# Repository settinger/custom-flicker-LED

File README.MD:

# A different interpretation of "programmable LED"

TL;DR I'm investigating if I can attach a very very small circuit to a through-hole LED to run a custom programmed pattern, similar to a candle-flicker LED.

## The Concept

A flicker LED is an LED that flickers. More specifically, it is a _drop-in replacement_ for a conventional LED—no need to change the current-limiting resistor, no new calculations for forward voltages, it works just the same as a conventional LED. And they're cheap, too! If you want an LED that flickers like a candle (or one that blinks at a set frequency and duty cycle) you are set for life.

But what if you want a different LED light pattern? In my specific case, I want an LED that turns on like a struggling fluorescent bulb. Or one that stays off most of the time, then suddenly lights up the room like lightning. Or a pseudo-status LED that blinks at random frequencies to trick the viewer into thinking some complex process is running. Or...anything, really. A programmable LED!

Do programmable LEDs like this exist? Obviously the WS2812b and similar LEDs exist, and those are frequently called "programmable LEDs". But those are pretty different than, say, a flicker LED. You still need a controller of some variety to tell the WS2812b what pattern to perform, which is not the case for a flicker LED, and not the case for the LEDs I'm envisioning.

## The Circuit

So can it be done? Without designing a custom IC and embedding it in a custom LED casing? I need a solution compatible with a stock LED. And that means the solution needs to exist _in parallel with the LED_. I'm envisioning a small PCB nestled underneath a 5mm through-hole LED. Soldered in place between the existing legs, no cuts or modifications to the LED itself.

What microcontroller is small enough to fit under a 5mm through-hole LED? I know of two: the WLCSP-12 ATtiny20 (1.55×1.43 mm) and the WLP-16 MAX32660 (1.55×1.57 mm). It's true that I've been meaning to get better with ARM systems, but for now I'll stick with the more familiar AVR-based ATtiny20.

Both those microcontrollers require at least 1.8V to operate. A white LED drawing between 1 and 20 mA will have a forward voltage in roughly the 2.4 - 3.1 V range. That means a microcontroller in parallel can be powered while the LED is on! However, if the LED shuts off, the voltage across it drops to 0V and the microcontroller will shut off as well. To get around this, we can make the LED super dim instead of completely turned off. If we use a shunt to get the LED forward voltage into the 1.8 - 2.0 V range, the microcontroller can stay on while the LED light output is undetectable. A TLVH431 adjustable shunt lets us keep the same forward voltage, regardless of if the shunt is carrying 1 mA or 20 mA, which makes things more consistent than a Zener diode can do.

My original plan was to shunt current around the LED using a BJT driven by an I/O pin on the microcontroller. This would be paired with a Zener diode to keep the LED voltage at at least 1.8V, to ensure the microcontroller has enough power. There were some issues with this approach! For one thing, I learned that low-value Zeners have much more variation in their breakdown voltages. A diode sold as a 1.8V Zener might, at a current of 10 mA, have a breakdown voltage closer to 2.6V; this wouldn't dim the LED at all!

Another issue was the transistor. I didn't realize that I could sink ~20 mA directly into these microcontrollers' GPIO pins! In fact, the ATtiny20 GPIO can source/sink 40 mA, and the MAX32660 can do 25. This means the current being diverted around the LED can go through the microcontroller, instead of an external transistor. Thank you to [cpldcpu](https://cpldcpu.wordpress.com) for pointing this out to me! I don't know what led me to think that a BGA ATtiny could handle less current than SOIC or DIP equivalents. That set off a cascade of design adjustments that led to the current very-low-component-count design.

## Putting it together

It's working! [Here is a video of the flicker in action](https://twitter.com/DHammarskjold/status/1491195660074627072). The flicker animation is a port of one kindly provided by [Emily Velasco](https://twitter.com/MLE_Online), which you can obtain in the `code/` folder.

[As you can see here](https://twitter.com/DHammarskjold/status/1490858013917208579), there was a (relatively) large PCB still attached to the LED. Those are the programming pads, so I can tweak the program on the ATtiny20 until I decide to trim off the excess parts.

There are components on both sides of the PCB. I put the ATtiny20 and TLVH431 on first, using a hot plate. Then I programmed the tiny20, and finally I hand-soldered the 0402 passives. I used a 47kΩ and a 68kΩ resistor instead of the desired 4.7kΩ and 7.5kΩ ones because that's what I had on hand.

[Here is a tweet showing my protoboard circuit](https://twitter.com/DHammarskjold/status/1483334537580998658), working as expected with larger versions of each part. This helped me dial in the right resistor values and measure the range of current that kept the board functioning. According to my cheap ammeter, the microcontroller functions properly on a supply as low as 0.5 mA and as high as 20 mA, which I'm thrilled to see.

Please let me know if you have some suggestions for improvements to the fluorescent-flicker animation, or if there are other programmable LED animations you'd like to see! I have a few ideas for a 5mm RGB LED, but that's a project for another time....

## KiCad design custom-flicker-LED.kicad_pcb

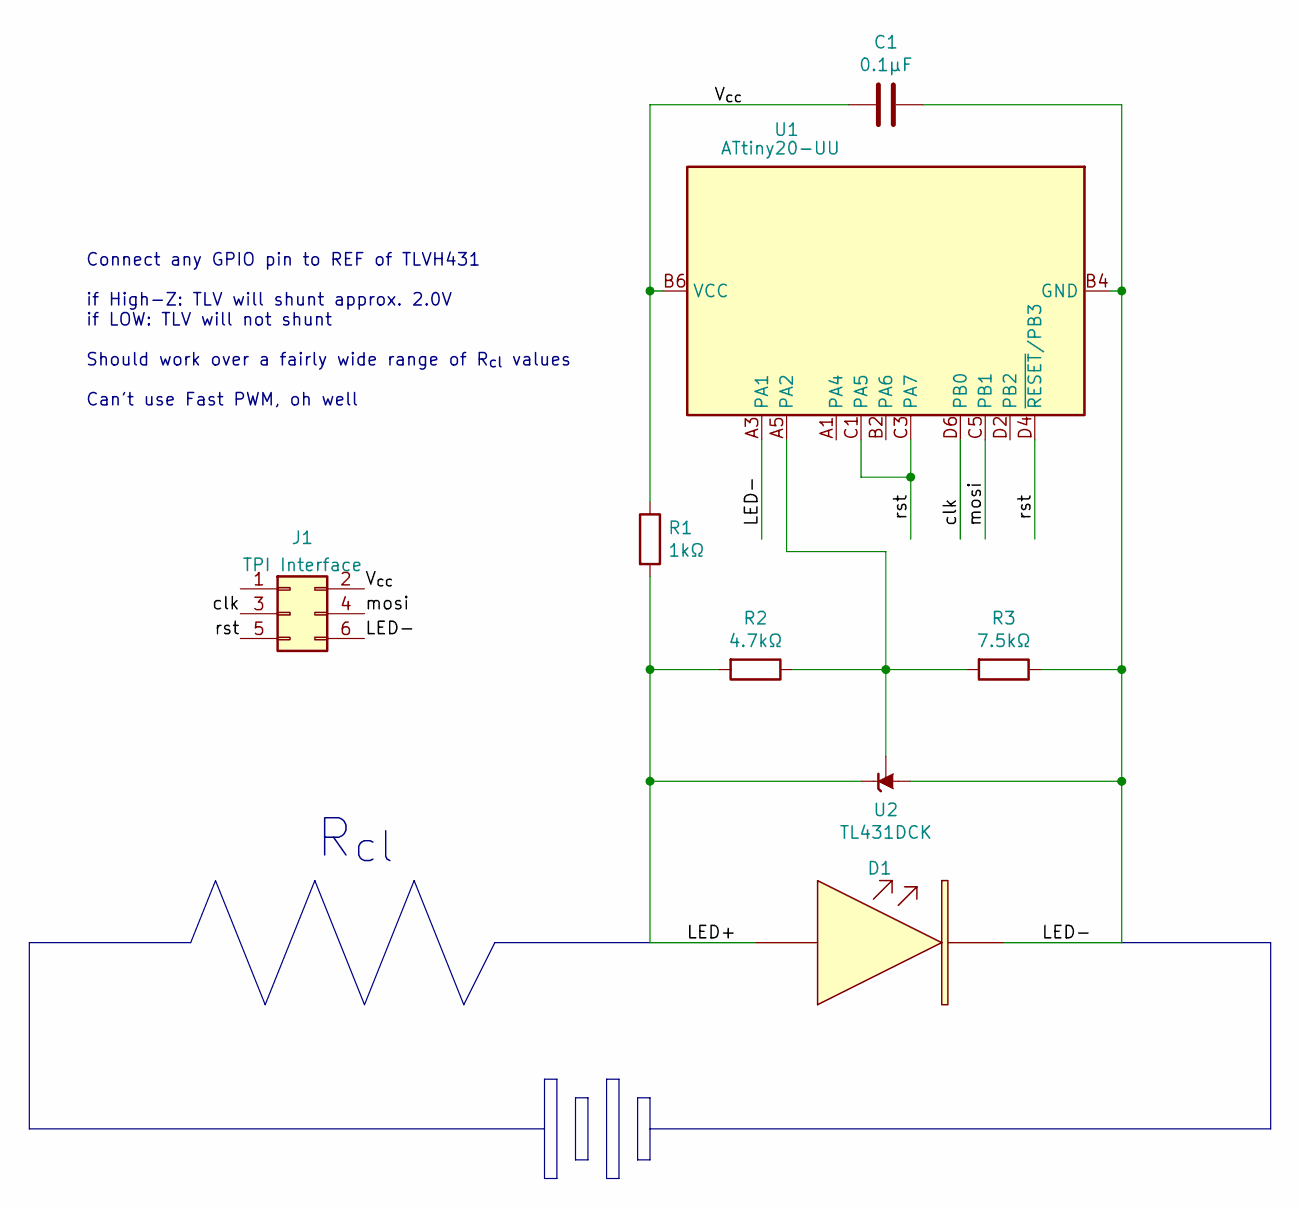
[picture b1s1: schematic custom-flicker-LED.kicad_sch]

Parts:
C1: 0.1μF; C_0402_1005Metric
D1: LED_big; LED_D5.0mm_Clear
J1: TPI Interface; PinHeader_2x03_P2.54mm_Vertical
R1: 1kΩ; R_0402_1005Metric
R2: 4.7kΩ; R_0402_1005Metric
R3: 7.5kΩ; R_0402_1005Metric
U1: ATtiny20-UU; WLCSP-12_1.403x1.555mm_P0.4mm_Stagger
U2: TL431DCK; SOT-363_SC-70-6

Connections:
/LED+: D1.2 (A), R1.2, R2.2, U2.1 (K)
/LED-: C1.1, D1.1 (K), J1.6, R3.1, U1.A3 (PA1), U1.B4 (GND), U2.6 (A)
/V_{cc}: C1.2, J1.2, R1.1, U1.B6 (VCC)
/clk: J1.3, U1.D6 (PB0)
/mosi: J1.4, U1.C5 (PB1)
/rst: J1.5, U1.C1 (PA5), U1.C3 (PA7), U1.D4 (~RESET/PB3)
unnamed: R2.1, R3.2, U1.A5 (PA2), U2.3 (REF)

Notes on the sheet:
R_{cl}
Connect any GPIO pin to REF of TLVH431 if High-Z: TLV will shunt approx. 2.0V if LOW: TLV will not shunt Should work over a fairly wide range of R_{cl} values Can't use Fast PWM, oh well

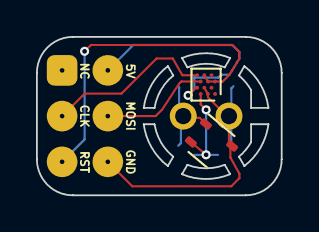
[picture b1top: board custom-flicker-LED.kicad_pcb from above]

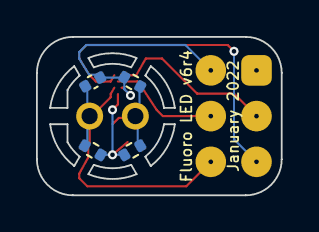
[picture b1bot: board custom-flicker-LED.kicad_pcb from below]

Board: 2 copper layers, 13.6 x 8.8 mm, 8 parts (5 on the bottom side), 7 nets.

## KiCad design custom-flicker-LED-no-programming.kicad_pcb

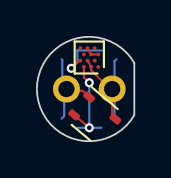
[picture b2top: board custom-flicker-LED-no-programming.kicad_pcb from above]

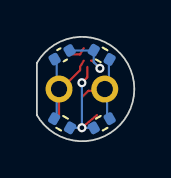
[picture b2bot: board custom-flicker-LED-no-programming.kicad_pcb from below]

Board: 2 copper layers, 5.4 x 5.8 mm, 7 parts (5 on the bottom side), 5 nets.

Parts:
C1: 0.1μF; C_0402_1005Metric
D1: LED_big; LED_D5.0mm_Clear
R1: 1kΩ; R_0402_1005Metric
R2: 4.5kΩ; R_0402_1005Metric
R3: 7.5kΩ; R_0402_1005Metric
U1: ATtiny20-UU; WLCSP-12_1.403x1.555mm_P0.4mm_Stagger
U2: TL431DCK; SOT-363_SC-70-6

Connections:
/LED+: D1.2 (A), R1.2, R2.2, U2.1 (K)
/LED-: C1.1, D1.1 (K), R3.1, U1.A3 (PA1), U1.B4 (GND), U2.6 (A)
/V_{cc}: C1.2, R1.1, U1.B6 (VCC)
/rst: U1.C1 (PA5), U1.C3 (PA7), U1.D4 (~RESET/PB3)
unnamed: R2.1, R3.2, U1.A5 (PA2), U2.3 (REF)

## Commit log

2021-12-20 First public commit
2022-01-24 Migrated to KiCad 6 and a much better circuit
2022-01-24 Added flicker code
2022-01-24 typo
2022-01-24 fixed embarrassing typo
2022-02-08 Update to show it working IRL, wooooo
2022-02-08 Improved code a bit
2022-02-10 I'm calling this done (except I still want to do the Quake lights thing)
